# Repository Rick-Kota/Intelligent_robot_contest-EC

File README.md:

Intelligent_robot_contest-Kanade-

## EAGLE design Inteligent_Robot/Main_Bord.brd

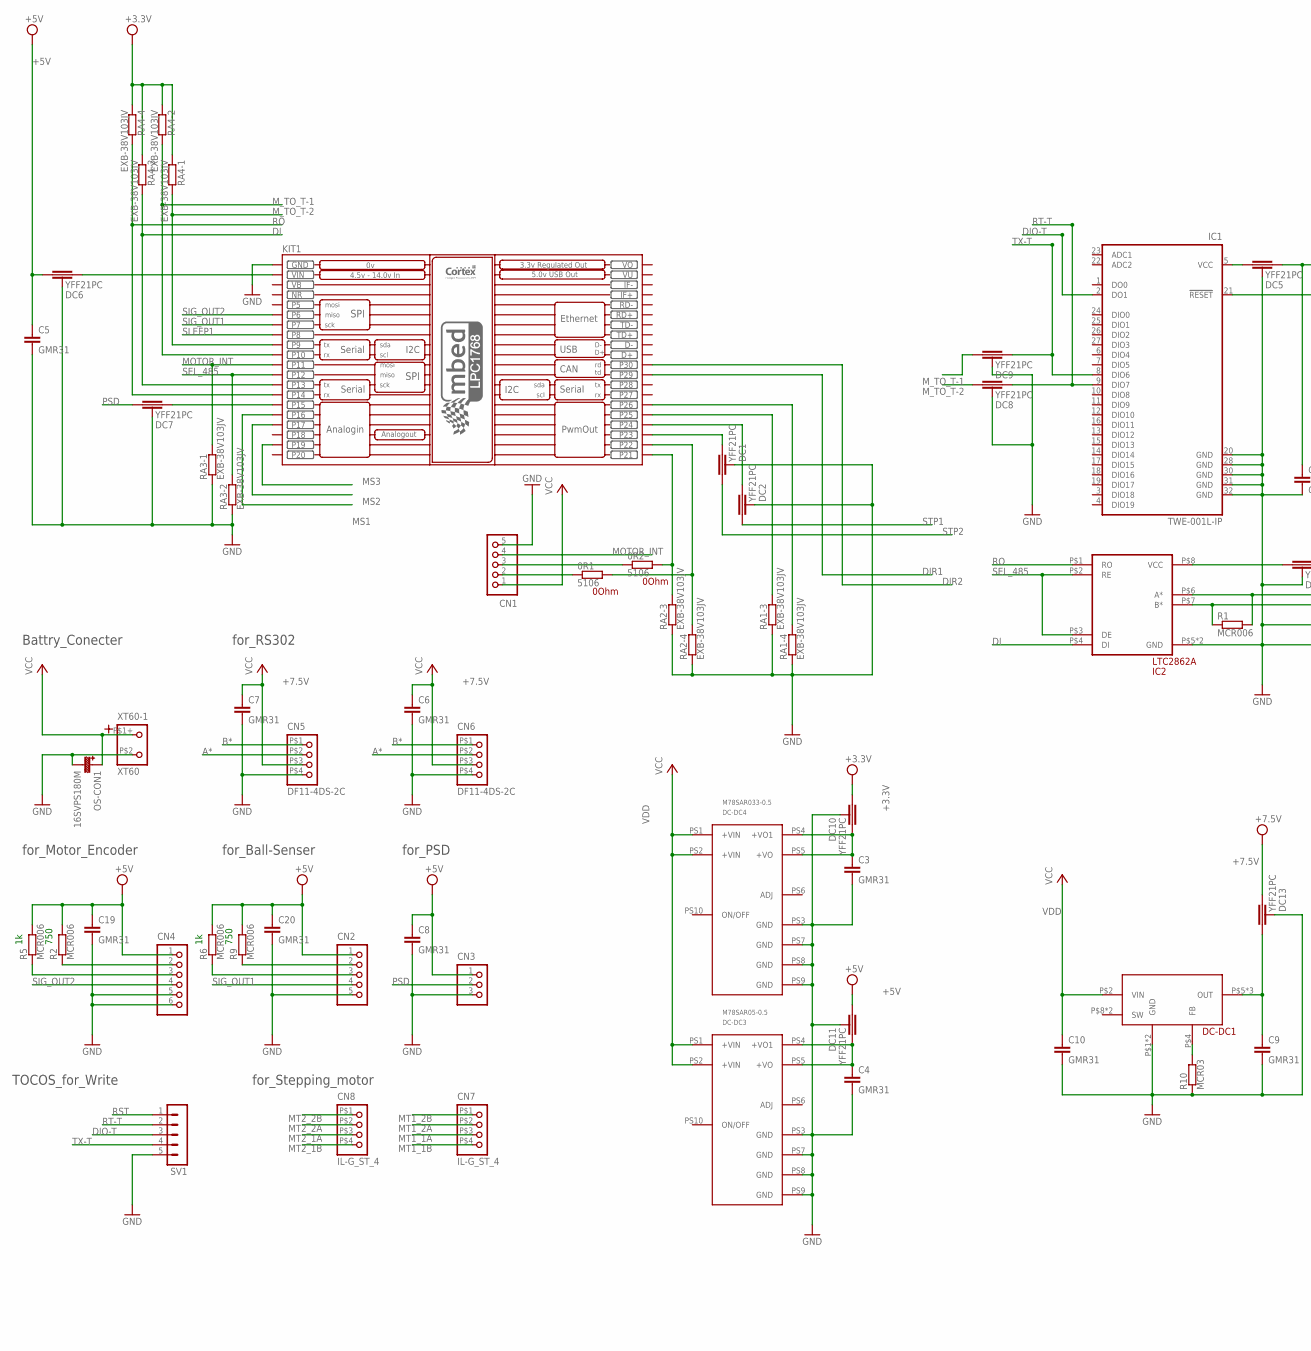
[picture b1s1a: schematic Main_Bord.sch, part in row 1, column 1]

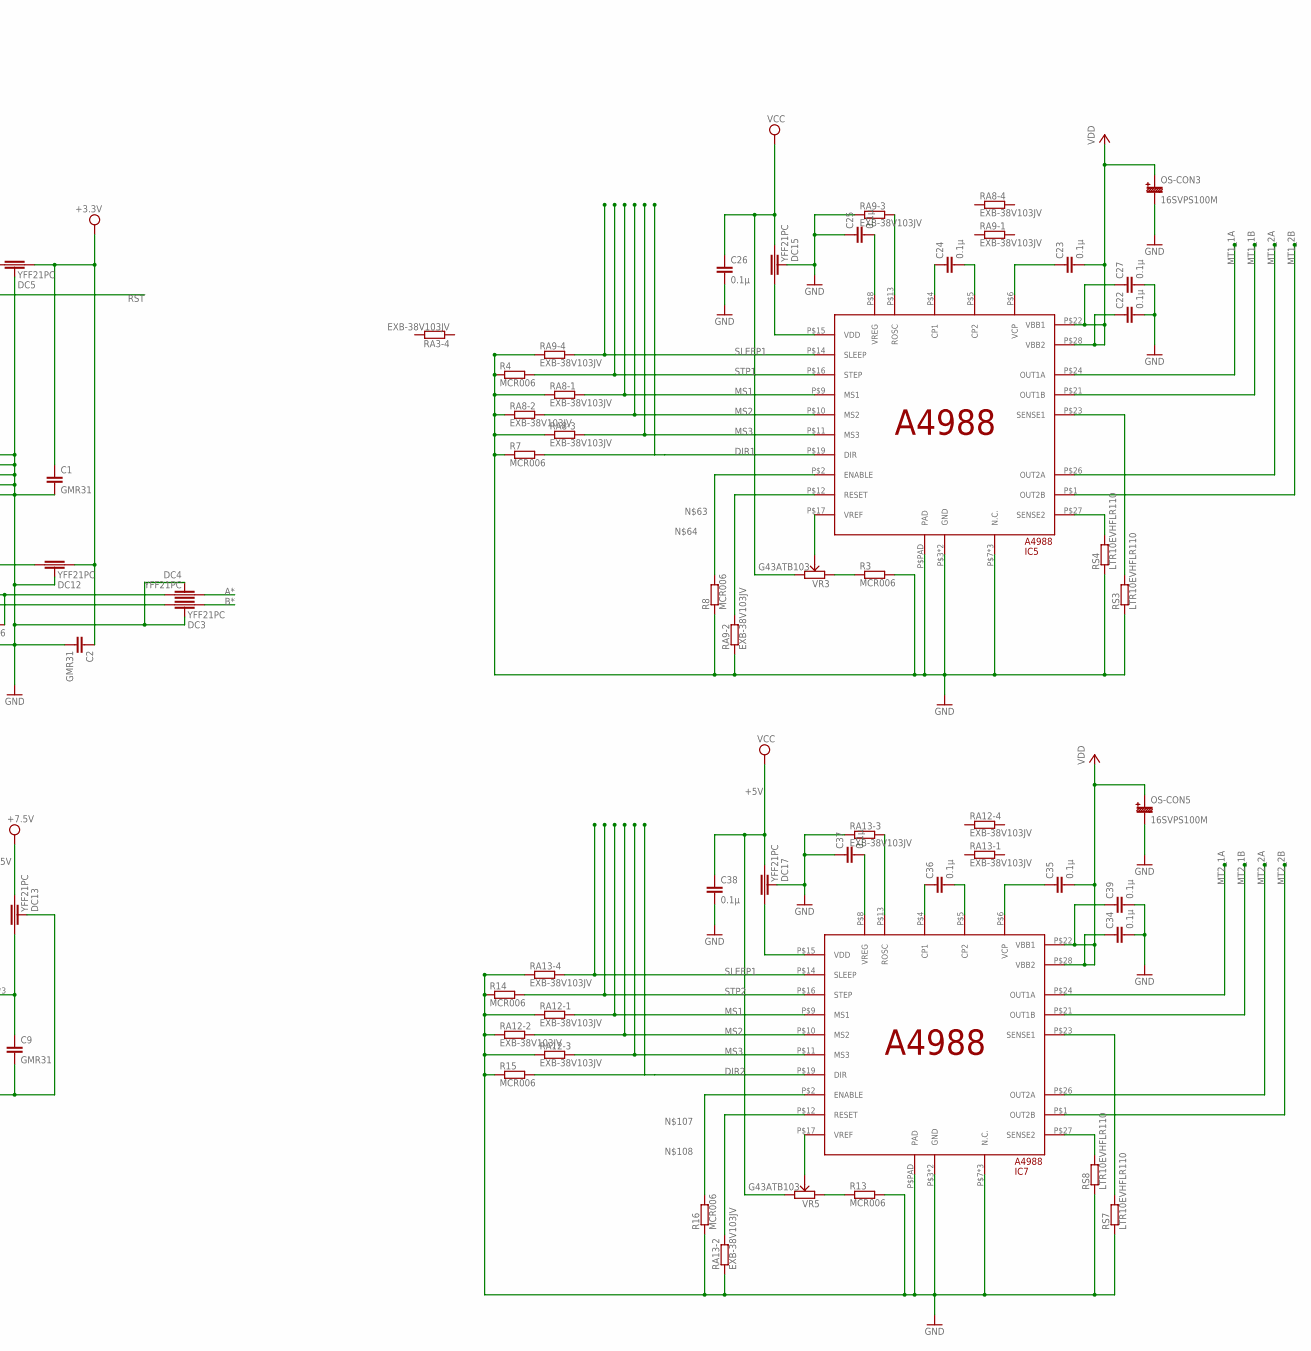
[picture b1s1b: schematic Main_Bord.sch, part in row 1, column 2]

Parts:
0R1, 0R2: 5106; 5106JUMP_0805
C1, C2, C3, C4, C5, C6, C7, C8, C9, C10, C19, C20: GMR31
C22, C23, C24, C25, C26, C27, C34, C35, C36, C37, C38, C39: 0.1μ; GRM03
CN1, CN2: B5B-XH-A
CN3: B3B-XH-A
CN4: B6B-XH-A
CN5, CN6: DF11-4DS-2C
CN7, CN8: IL-G_ST_4; IL-G_V-4
DC1, DC2, DC3, DC4, DC5, DC6, DC7, DC8, DC9, DC10, DC11, DC12, DC13, DC15, DC17: YFF21PC
DC-DC1: MPM01; MPM00_V
DC-DC3: M78SAR05-0.5; M78SAR
DC-DC4: M78SAR033-0.5; M78SAR
IC1: TWE-001L-IP; QFN32
IC2: LTC2862A; DD_PACKGE_8
IC5, IC7: A4988; ET_PACKGE,28PIN_WITH_EXPAD
KIT1: MBED_NXP_LPC1768; MBED-KIT
OS-CON1: 16SVPS180M; SVCP_F8
OS-CON3, OS-CON5: 16SVPS100M; SVCP_F8
R1, R2, R3, R4, R5, R6, R7, R8, R9, R13, R14, R15, R16: MCR006
R10: MCR03
RA1, RA2, RA3, RA4, RA8, RA9, RA12, RA13: EXB-38V103JV; EXB-38V,28V
RS3, RS4, RS7, RS8: LTR10EVHFLR110; LTR10
SV1: MA05-1
VR3, VR5: G43ATB103; G43A
XT60-1: XT60

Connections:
+3.3V: C1.P$1 (1), C2.P$1 (1), DC5.P$2, DC10.P$1, DC12.P$2, RA4.P$5 (2), RA4.P$6 (2), RA4.P$7 (2), RA4.P$8 (2)
+5V: C5.P$1 (1), C8.P$1 (1), C19.P$1 (1), C20.P$1 (1), C26.P$1 (1), C38.P$1 (1), CN2.1, CN3.1, CN4.1, DC6.P$1, DC11.P$1, DC15.P$2, DC17.P$2, R2.P$1 (1), R5.P$1 (1), R6.P$1 (1), R9.P$1 (1), VR3.P$2 (1), VR5.P$2 (1)
+7.5V: C6.P$1 (1), C7.P$1 (1), CN5.P$3 (3), CN6.P$3 (3), DC13.P$2
A*: CN5.P$2 (2), CN6.P$2 (2), DC4.P$1
B*: CN5.P$1 (1), CN6.P$1 (1), DC3.P$2
DI: IC2.P$4 (DI), KIT1.P$13 (P13), RA4.P$3 (1)
DIO-T: IC1.2 (DO1), SV1.3
DIR1: IC5.P$19 (DIR), KIT1.P$29 (P29), R7.P$1 (1)
DIR2: IC7.P$19 (DIR), KIT1.P$30 (P30), R15.P$1 (1)
DIR5: IC5.P$23 (SENSE1), RS3.P$1 (1)
DIR7: IC7.P$23 (SENSE1), RS7.P$1 (1)
GND: C1.P$2 (2), C2.P$2 (2), C3.P$2 (2), C4.P$2 (2), C5.P$2 (2), C6.P$2 (2), C7.P$2 (2), C8.P$2 (2), C9.P$2 (2), C10.P$2 (2), C19.P$2 (2), C20.P$2 (2), C22.P$2 (2), C25.P$1 (1), C26.P$2 (2), C27.P$2 (2), C34.P$2 (2), C37.P$1 (1), C38.P$2 (2), C39.P$2 (2), CN1.5, CN2.5, CN3.3, CN4.5, CN4.6, CN5.P$4 (4), CN6.P$4 (4), DC1.GND1 (GND), DC1.GND2 (GND), DC2.GND1 (GND), DC2.GND2 (GND), DC3.GND1 (GND), DC3.GND2 (GND), DC4.GND1 (GND), DC4.GND2 (GND), DC5.GND1 (GND), DC5.GND2 (GND), DC6.GND1 (GND), DC6.GND2 (GND), DC7.GND1 (GND), DC7.GND2 (GND), DC8.GND1 (GND), DC8.GND2 (GND), DC9.GND1 (GND), DC9.GND2 (GND), DC10.GND1 (GND), DC10.GND2 (GND), DC11.GND1 (GND), DC11.GND2 (GND), DC12.GND1 (GND), DC12.GND2 (GND), DC13.GND1 (GND), DC13.GND2 (GND), DC15.GND1 (GND), DC15.GND2 (GND), DC17.GND1 (GND), DC17.GND2 (GND), DC-DC1.P$1 (GND), DC-DC1.P$3 (GND), DC-DC3.PS3 (GND), DC-DC3.PS7 (GND), DC-DC3.PS8 (GND), DC-DC3.PS9 (GND), DC-DC4.PS3 (GND), DC-DC4.PS7 (GND), DC-DC4.PS8 (GND), DC-DC4.PS9 (GND), IC1.20 (GND), IC1.28 (GND), IC1.30 (GND), IC1.31 (GND), IC1.32 (GND), IC2.P$5 (GND), IC2.PAD (GND), IC5.P$3 (GND), IC5.P$7 (N.C.), IC5.P$18 (GND), IC5.P$20 (N.C.), IC5.P$25 (N.C.), IC5.P$PAD (PAD), IC7.P$3 (GND), IC7.P$7 (N.C.), IC7.P$18 (GND), IC7.P$20 (N.C.), IC7.P$25 (N.C.), IC7.P$PAD (PAD), KIT1.GND, OS-CON1.P$1 (2), OS-CON3.P$1 (2), OS-CON5.P$1 (2), R3.P$1 (1), R4.P$2 (2), R7.P$2 (2), R8.P$2 (2), R10.P$2 (2), R13.P$1 (1), R14.P$2 (2), R15.P$2 (2), R16.P$2 (2), RA1.P$5 (2), RA1.P$6 (2), RA2.P$5 (2), RA2.P$6 (2), RA3.P$7 (2), RA3.P$8 (2), RA8.P$6 (2), RA8.P$7 (2), RA8.P$8 (2), RA9.P$5 (2), RA9.P$6 (2), RA9.P$7 (2), RA12.P$6 (2), RA12.P$7 (2), RA12.P$8 (2), RA13.P$5 (2), RA13.P$6 (2), RA13.P$7 (2), RS3.P$2 (2), RS4.P$2 (2), RS7.P$2 (2), RS8.P$2 (2), SV1.5, XT60-1.P$2 (2)
MOTOR_INT: CN1.4, KIT1.P$11 (P11), RA3.P$1 (1)
MS1: IC5.P$9 (MS1), IC7.P$9 (MS1), KIT1.P$16 (P16), RA8.P$1 (1), RA12.P$1 (1)
MS2: IC5.P$10 (MS2), IC7.P$10 (MS2), KIT1.P$17 (P17), RA8.P$2 (1), RA12.P$2 (1)
MS3: IC5.P$11 (MS3), IC7.P$11 (MS3), KIT1.P$19 (P19), RA8.P$3 (1), RA12.P$3 (1)
MT1_1A: CN7.P$3 (3), IC5.P$24 (OUT1A)
MT1_1B: CN7.P$4 (4), IC5.P$21 (OUT1B)
MT1_2A: CN7.P$2 (2), IC5.P$26 (OUT2A)
MT1_2B: CN7.P$1 (1), IC5.P$1 (OUT2B)
MT2_1A: CN8.P$3 (3), IC7.P$24 (OUT1A)
MT2_1B: CN8.P$4 (4), IC7.P$21 (OUT1B)
MT2_2A: CN8.P$2 (2), IC7.P$26 (OUT2A)
MT2_2B: CN8.P$1 (1), IC7.P$1 (OUT2B)
M_TO_T-1: DC9.P$1, KIT1.P$10 (P10), RA4.P$2 (1)
M_TO_T-2: DC8.P$1, KIT1.P$9 (P9), RA4.P$1 (1)
unnamed: 0R2.P$1 (1), KIT1.P$21 (P21), RA2.P$3 (1)
unnamed: 0R1.P$1 (1), KIT1.P$22 (P22), RA2.P$4 (1)
unnamed: DC6.P$2, KIT1.VIN
unnamed: DC5.P$1, IC1.5 (VCC)
unnamed: DC7.P$2, KIT1.P$15 (P15)
unnamed: C9.P$1 (1), DC13.P$1, DC-DC1.P$5 (OUT), DC-DC1.P$6 (OUT), DC-DC1.P$7 (OUT)
unnamed: KIT1.P$25 (P25), RA1.P$3 (1)
unnamed: KIT1.P$26 (P26), RA1.P$4 (1)
unnamed: DC-DC1.P$4 (FB), R10.P$1 (1)
unnamed: 0R2.P$2 (2), CN1.3
unnamed: 0R1.P$2 (2), CN1.2
unnamed: C3.P$1 (1), DC10.P$2, DC-DC4.PS4 (+VO1), DC-DC4.PS5 (+VO)
unnamed: DC4.P$2, IC2.P$6 (A*), R1.P$1 (1)
unnamed: DC3.P$1, IC2.P$7 (B*), R1.P$2 (2)
unnamed: DC2.P$2, KIT1.P$24 (P24)
unnamed: DC1.P$2, KIT1.P$23 (P23)
unnamed: CN2.2, R9.P$2 (2)
unnamed: CN2.3, R6.P$2 (2)
unnamed: CN4.2, R2.P$2 (2)
unnamed: CN4.3, R5.P$2 (2)
unnamed: C4.P$1 (1), DC11.P$2, DC-DC3.PS4 (+VO1), DC-DC3.PS5 (+VO)
unnamed: DC12.P$1, IC2.P$8 (VCC)
unnamed: C23.P$1 (1), IC5.P$6 (VCP)
unnamed: C24.P$1 (1), IC5.P$4 (CP1)
unnamed: C24.P$2 (2), IC5.P$5 (CP2)
unnamed: IC5.P$27 (SENSE2), RS4.P$1 (1)
unnamed: C25.P$2 (2), IC5.P$8 (VREG)
unnamed: IC5.P$13 (ROSC), RA9.P$3 (1)
unnamed: IC5.P$2 (ENABLE), R8.P$1 (1)
unnamed: IC5.P$12 (RESET), RA9.P$2 (1)
unnamed: R3.P$2 (2), VR3.P$3 (2)
unnamed: IC5.P$17 (VREF), VR3.P$1 (IO3)
unnamed: DC15.P$1, IC5.P$15 (VDD)
unnamed: C35.P$1 (1), IC7.P$6 (VCP)
unnamed: C36.P$1 (1), IC7.P$4 (CP1)
unnamed: C36.P$2 (2), IC7.P$5 (CP2)
unnamed: IC7.P$27 (SENSE2), RS8.P$1 (1)
unnamed: C37.P$2 (2), IC7.P$8 (VREG)
unnamed: IC7.P$13 (ROSC), RA13.P$3 (1)
unnamed: IC7.P$2 (ENABLE), R16.P$1 (1)
unnamed: IC7.P$12 (RESET), RA13.P$2 (1)
unnamed: R13.P$2 (2), VR5.P$3 (2)
unnamed: IC7.P$17 (VREF), VR5.P$1 (IO3)
unnamed: DC17.P$1, IC7.P$15 (VDD)
NR: KIT1.NR
PSD: CN3.2, DC7.P$1
RO: IC2.P$1 (RO), KIT1.P$14 (P14), RA4.P$4 (1)
RST: IC1.21 (!RESET), SV1.1
RT-T: DC8.P$2, IC1.9 (DIO7), SV1.2
SEL_485: IC2.P$2 (RE), IC2.P$3 (DE), KIT1.P$12 (P12), RA3.P$2 (1)
SIG_OUT1: CN2.4, KIT1.P$7 (P7)
SIG_OUT2: CN4.4, KIT1.P$6 (P6)
SLEEP1: IC5.P$14 (SLEEP), IC7.P$14 (SLEEP), KIT1.P$8 (P8), RA9.P$4 (1), RA13.P$4 (1)
STP1: DC2.P$1, IC5.P$16 (STEP), R4.P$1 (1)
STP2: DC1.P$1, IC7.P$16 (STEP), R14.P$1 (1)
TX-T: DC9.P$2, IC1.8 (DIO6), SV1.4
VB: KIT1.VB
VDD: C10.P$1 (1), C22.P$1 (1), C23.P$2 (2), C27.P$1 (1), C34.P$1 (1), C35.P$2 (2), C39.P$1 (1), CN1.1, DC-DC1.P$2 (VIN), DC-DC3.PS1 (+VIN), DC-DC3.PS2 (+VIN), DC-DC4.PS1 (+VIN), DC-DC4.PS2 (+VIN), IC5.P$22 (VBB1), IC5.P$28 (VBB2), IC7.P$22 (VBB1), IC7.P$28 (VBB2), OS-CON1.P$2+ (+), OS-CON3.P$2+ (+), OS-CON5.P$2+ (+), XT60-1.P$1+ (1+)
VO: KIT1.VOUT (VO)
VU: KIT1.VU

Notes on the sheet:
750
TOCOS_for_Write
for_Stepping_motor
for_PSD
for_Ball-Senser
for_Motor_Encoder
for_RS302
Battry_Conecter

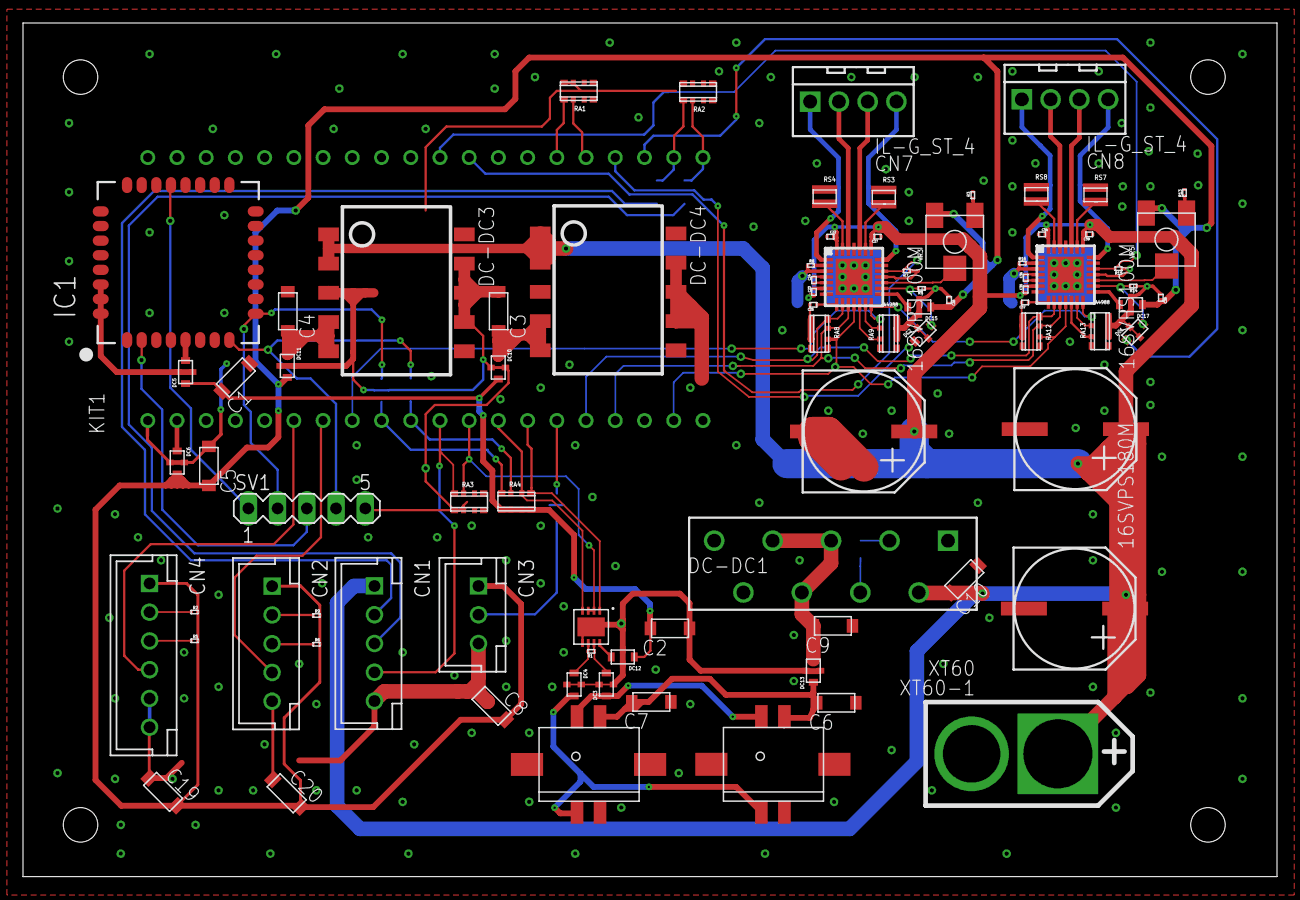
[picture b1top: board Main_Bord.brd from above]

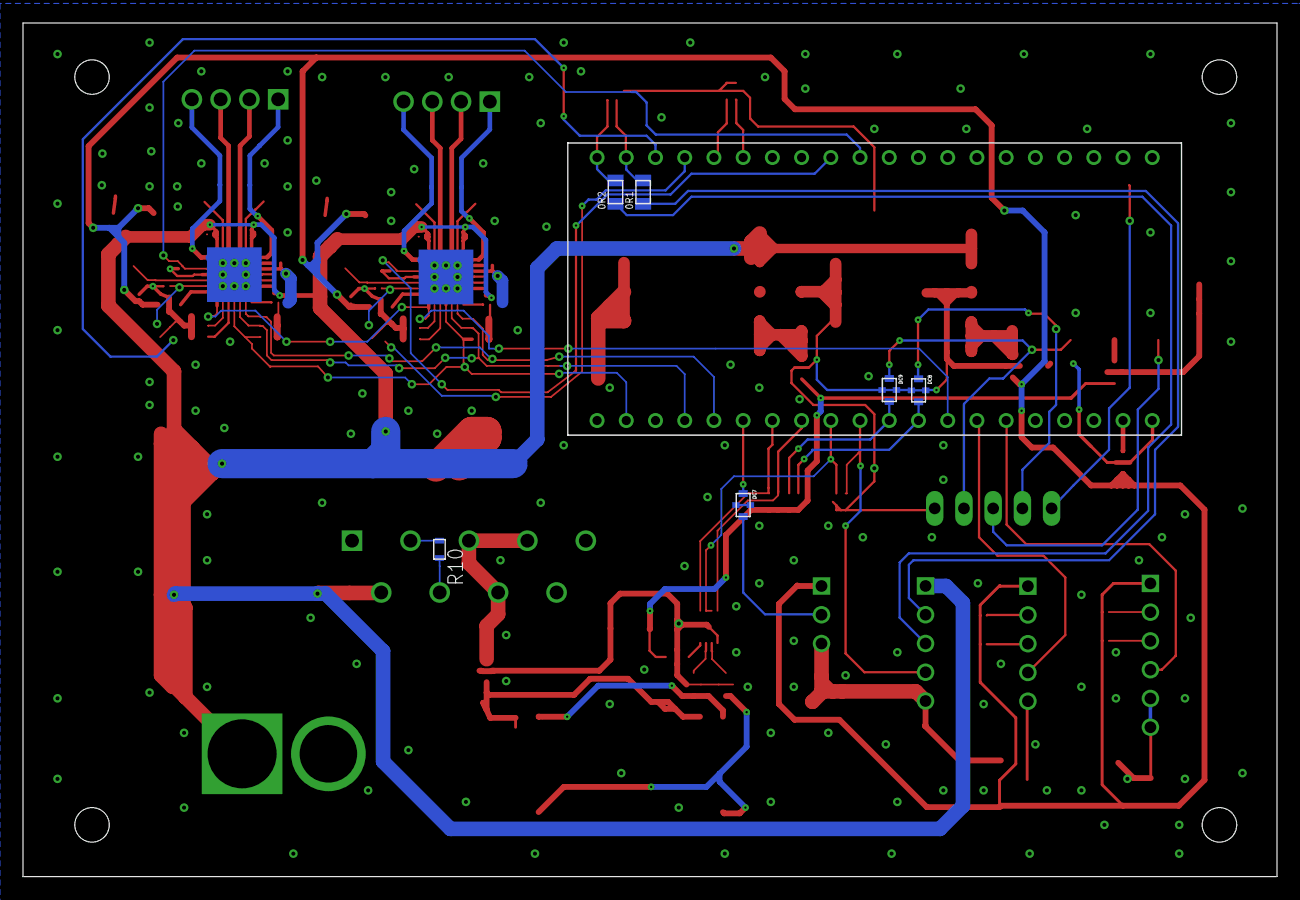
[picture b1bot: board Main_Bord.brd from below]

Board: 2 copper layers, 109.0 x 74.2 mm, 90 parts (6 on the bottom side), 82 nets.

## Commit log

2017-10-08 Add In development files
2017-10-09 Add Disign Block "A4988"
2017-10-09 Complate A4988 Block
2017-10-09 Start Print section
2017-10-09 Complete_First_version
2017-10-15 Ver2
2018-01-19 New Lib
    Keystone 0ohm resister
2018-01-19 Fix pin position
2018-01-19 Refime pisitions
2018-01-19 Refine finshed
2018-01-19 Update .gitignore
    ignore to mac's systemfile
2018-01-19 temp
2018-01-21 Add Groung solid pattern
